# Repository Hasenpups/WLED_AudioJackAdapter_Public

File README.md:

Shield: [![CC BY-NC-SA 4.0][cc-by-nc-sa-shield]][cc-by-nc-sa]

This work is licensed under a
[Creative Commons Attribution-NonCommercial-ShareAlike 4.0 International License][cc-by-nc-sa].

[![CC BY-NC-SA 4.0][cc-by-nc-sa-image]][cc-by-nc-sa]

[cc-by-nc-sa]: http://creativecommons.org/licenses/by-nc-sa/4.0/
[cc-by-nc-sa-image]: https://licensebuttons.net/l/by-nc-sa/4.0/88x31.png
[cc-by-nc-sa-shield]: https://img.shields.io/badge/License-CC%20BY--NC--SA%204.0-lightgrey.svg

## Donations / Spenden
If somebody wants to support me for upcoming projects :)  
- PayPal:  
- Amazon Giftcard: https://www.amazon.de/Amazon-Gutschein-per-E-Mail-Amazon/dp/B0054PDOV8 - stefan.riese@me.com

# WLED_AudioJackAdapter

## Features
- Connect 3.5mm audio jack to WLED controller input pin

## BOM
- J1: Audio Jack PJ320D - https://www.ebay.de/itm/393422313034
- J2: 3-pin header male
- C1, C2: 100nF 0805
- R1, R2: 680 Ohm 0805
- R3, R4: 1M Ohm 0805

## Wiring diagram
- https://github.com/Hasenpups/WLED_AudioJackAdapter_Public/blob/main/WLED_AudioJackAdapter.pdf

## References
- Sound reactive WLED: https://github.com/atuline/WLED/releases
- Wiring example: https://github.com/atuline/WLED/wiki/Analog-Audio-Input-Options

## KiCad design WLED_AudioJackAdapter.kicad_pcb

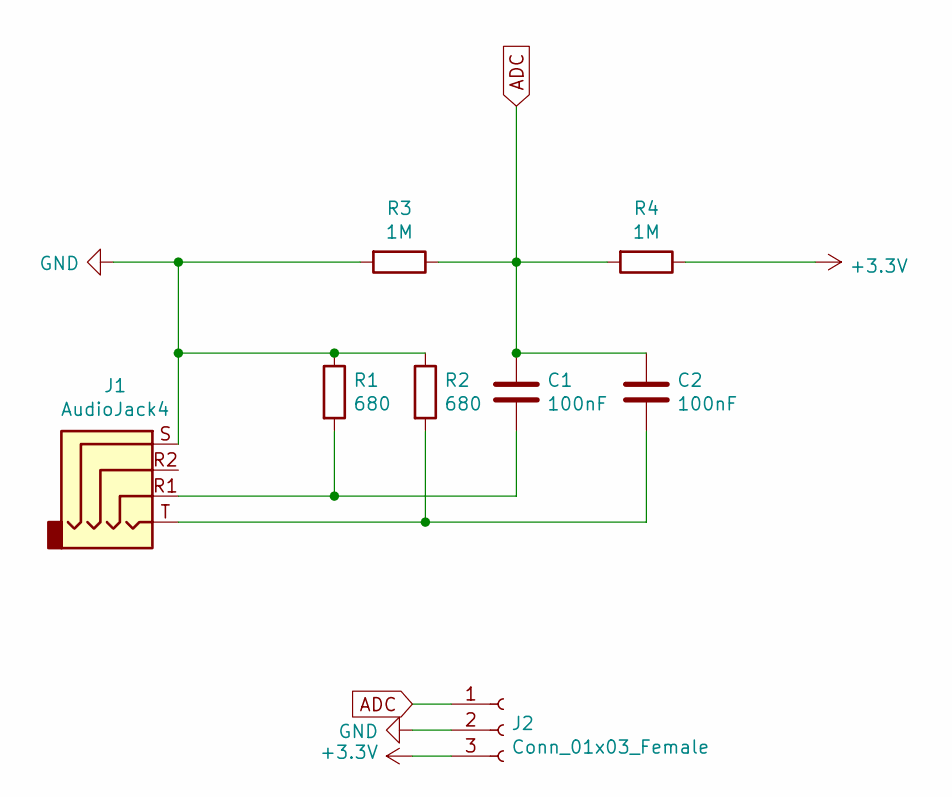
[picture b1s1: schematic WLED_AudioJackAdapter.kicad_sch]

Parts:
C1, C2: 100nF; C_0805_2012Metric_Pad1.18x1.45mm_HandSolder
J1: AudioJack4; Jack_3.5mm_PJ320D_Horizontal
J2: Conn_01x03_Female; PinHeader_1x03_P2.54mm_Vertical
R1, R2: 680; R_0805_2012Metric_Pad1.20x1.40mm_HandSolder
R3, R4: 1M; R_0805_2012Metric_Pad1.20x1.40mm_HandSolder

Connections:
+3V3: J2.3, R4.1
ADC: C1.1, C2.1, J2.1, R3.1, R4.2
GND: J1.S, J2.2, R1.1, R2.1, R3.2
unnamed: C1.2, J1.R1, R1.2
unnamed: C2.2, J1.T, R2.2

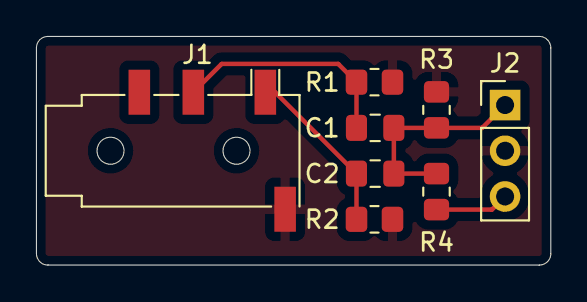
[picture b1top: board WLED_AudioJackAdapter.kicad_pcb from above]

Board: 2 copper layers, 28.6 x 12.7 mm, 8 parts (0 on the bottom side), 5 nets.

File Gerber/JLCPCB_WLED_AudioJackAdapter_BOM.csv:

Comment,Designator,Footprint,LCSC
"100nF","C1,C2","Capacitor_SMD:C_0805_2012Metric_Pad1.18x1.45mm_HandSolder","C29926"
"AudioJack4","J1","Connector_Audio:Jack_3.5mm_PJ320D_Horizontal","C521460"
"Conn_01x03_Female","J2","Connector_PinHeader_2.54mm:PinHeader_1x03_P2.54mm_Vertical",""
"680","R1,R2","Resistor_SMD:R_0805_2012Metric_Pad1.20x1.40mm_HandSolder","C17798"
"1M","R3,R4","Resistor_SMD:R_0805_2012Metric_Pad1.20x1.40mm_HandSolder","C26115"

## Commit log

2022-01-05 - initial commit
2022-01-05 - add schematic
2022-01-18 Create LICENSE
2022-01-18 - add SMT assembly files for JLCPCB
2022-01-18 - remove single gerber files
2022-01-18 - add image
2022-02-07 - update README.md
2022-02-17 - update to kicad 6
